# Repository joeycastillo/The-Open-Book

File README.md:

# The Open Book: Project Reboot

**A note from the project creator:** The Open Book was my first real electronics project; the earliest designs date to late 2019. I have learned a lot since those early days, and as such, here three years later, I am hitting reset. At this time the repository contains a version of the Open Book designed around the Raspberry Pi Pico. It's optimized for low part count and easy hand assembly, but it runs on AAA batteries and may not be as svelte as some folks might prefer. At a later date, I hope to design a followup with built-in LiPo charging and a slimmer profile, but at this time, this version of the book is the quickest path to getting hardware in people's hands so that we can start hacking on firmware together.

For details on how to build, test and use Open Book, I've [made documentation available here](https://www.oddlyspecificobjects.com/projects/openbook/).

The original Open Book repository has been archived in a branch called [original](https://github.com/joeycastillo/The-Open-Book/tree/original).

[The Open Book firmware, called libros, is under development here](https://github.com/joeycastillo/libros). It's a goddamn mess in some ways, and in dire need of some documentation, but for the moment it does do the job of presenting a list of books stored on an SD card, and letting you read them. The canonical format for books is plain text with the book title on the first line, OR plain text plus some front matter and some ASCII control codes for chapter breaks and formatting, [as documented here](https://www.oddlyspecificobjects.com/projects/openbook/#advanced-text-formatting).

## Original Introduction

As a society, we need an open source device for reading. Books are among the most important documents of our culture, yet the most popular and widespread devices we have for reading — the Kobo, the Nook, the Kindle and even the iPad — are closed devices, operating as small moving parts in a set of giant closed platforms whose owners' interests are not always aligned with readers'.

The Open Book aims to be a simple device that anyone with a soldering iron can build for themselves. The Open Book should be comprehensible: the reader should be able to look at it and understand, at least in broad strokes, how it works. It should be extensible, so that a reader with different needs can write code and add accessories that make the book work for them. It should be global, supporting readers of books in all the languages of the world. Most of all, it should be open, so that anyone can take this design as a starting point and use it to build a better book.

## State of the Book

At this time, the Pi Pico book is in decent shape if you want to try your hand at building it yourself. You will need to have two custom things fabricated: the **Open Book Main Board** (which you can get as a bare PCB) and the **Castellated E-Paper Driver** module (which you'll want to have done as a PCBA job). All the files you will need to send out for this can be found in the **Fabrication Files** folder in the project root:

* Upload `OSO-BOOK-C1-04-rounded.zip` to your PCB fabrication house of choice. It is designed to be a two-layer, 1 mm thick PCB, and you can use either an ENIG or lead-free HASL finish.
* If you plan to use JLCPCB's economic PCBA service, upload all three files in `OSO-BOOK-C2-01` to JLCPCB. Opt for a 1 mm thick lead-free HASL finish. Note that the board is slightly wider than it needs to be, just to meet the minimum size requirements for this service.
* If you plan to use PCBWay's PCBA service, upload all three files in `OSO-BOOK-C2-02` to PCBWay. Once again, opt for a 1 mm thick lead-free HASL finish. 

Other Parts: 

* Two of these [side mount buttons](https://www.digikey.com/en/products/detail/würth-elektronik/434351045816/5209090)
* One of these [side-mount switches](https://www.digikey.com/en/products/detail/c-k/JS102011SAQN/1640095)
* One [MEM2075 MicroSD card slot](https://www.digikey.com/en/products/detail/gct/MEM2075-00-140-01-A/9859614)
* One [GD25Q16C Flash chip](https://www.digikey.com/en/products/detail/gigadevice-semiconductor-hk-limited/GD25Q16CTIGR/9484675) with SOIC / SOP8 footprint.
* One [Keystone 1022 dual AAA battery holder](https://www.digikey.com/en/products/detail/keystone-electronics/1022/2137859) (you can get clones on Aliexpress for cheap)
* Two P-channel MOSFETS with SOT23 footprint (I use the DMG3415)
* Two 10kΩ resistors with 1206 footprint.
* Two 10µF capacitors with 1206 footprint (rated voltage >=6.3V).
* One 1µF capacitor with 0805 footprint (rated voltage >=6.3V).
* Seven through-hole slim tactile buttons (3mm by 6mm; [TL1107 type](https://www.digikey.com/en/products/detail/e-switch/TL1107AF130WQ/378976))
* One [GDEW042T2 grayscale e-paper display](https://buy-lcd.com/products/42inch-e-inkanel-spi-interface-buy-eaper-display). (Don't get the tri-color version; it'll end in heartbreak)
* And finally, one [Raspberry Pi Pico](https://www.digikey.com/en/products/detail/raspberry-pi/SC0915/13624793) board

The Open Book is open source hardware: you should feel free to build one yourself, order parts for ten and do a workshop at your local maker space, or even buy parts for fifty and sell them as kits. 

Please steal this book.

I plan to add more documentation in the new year, but until then, [this half-hour video walks through building one Open Book board in real-time](https://archive.org/details/live-from-the-oddly-specific-kitchen-table-assembling-the-pcbway-official-sponso).

### Forking and tweaking the boards

* Design files for the Open Book main board can be found in the `OSO-BOOK-C1` folder. It's a KiCad project.
* Design files for the castellated e-paper driver module can be found in the `OSO-BOOK-C2` folder. Alas, they are Eagle projects that predate my move to KiCad. There are two versions: an older version that was successfully fabricated with JLCPCB's economic PCBA service (`OSO-BOOK-C2-01`), and a newer version successfully fabricated using PCBWay's PCBA service (`OSO-BOOK-C2-02`). Both work great.

## License

 Different components of the project are licensed differently, see [LICENSE.md](https://github.com/joeycastillo/The-Open-Book/blob/main/LICENSE.md).

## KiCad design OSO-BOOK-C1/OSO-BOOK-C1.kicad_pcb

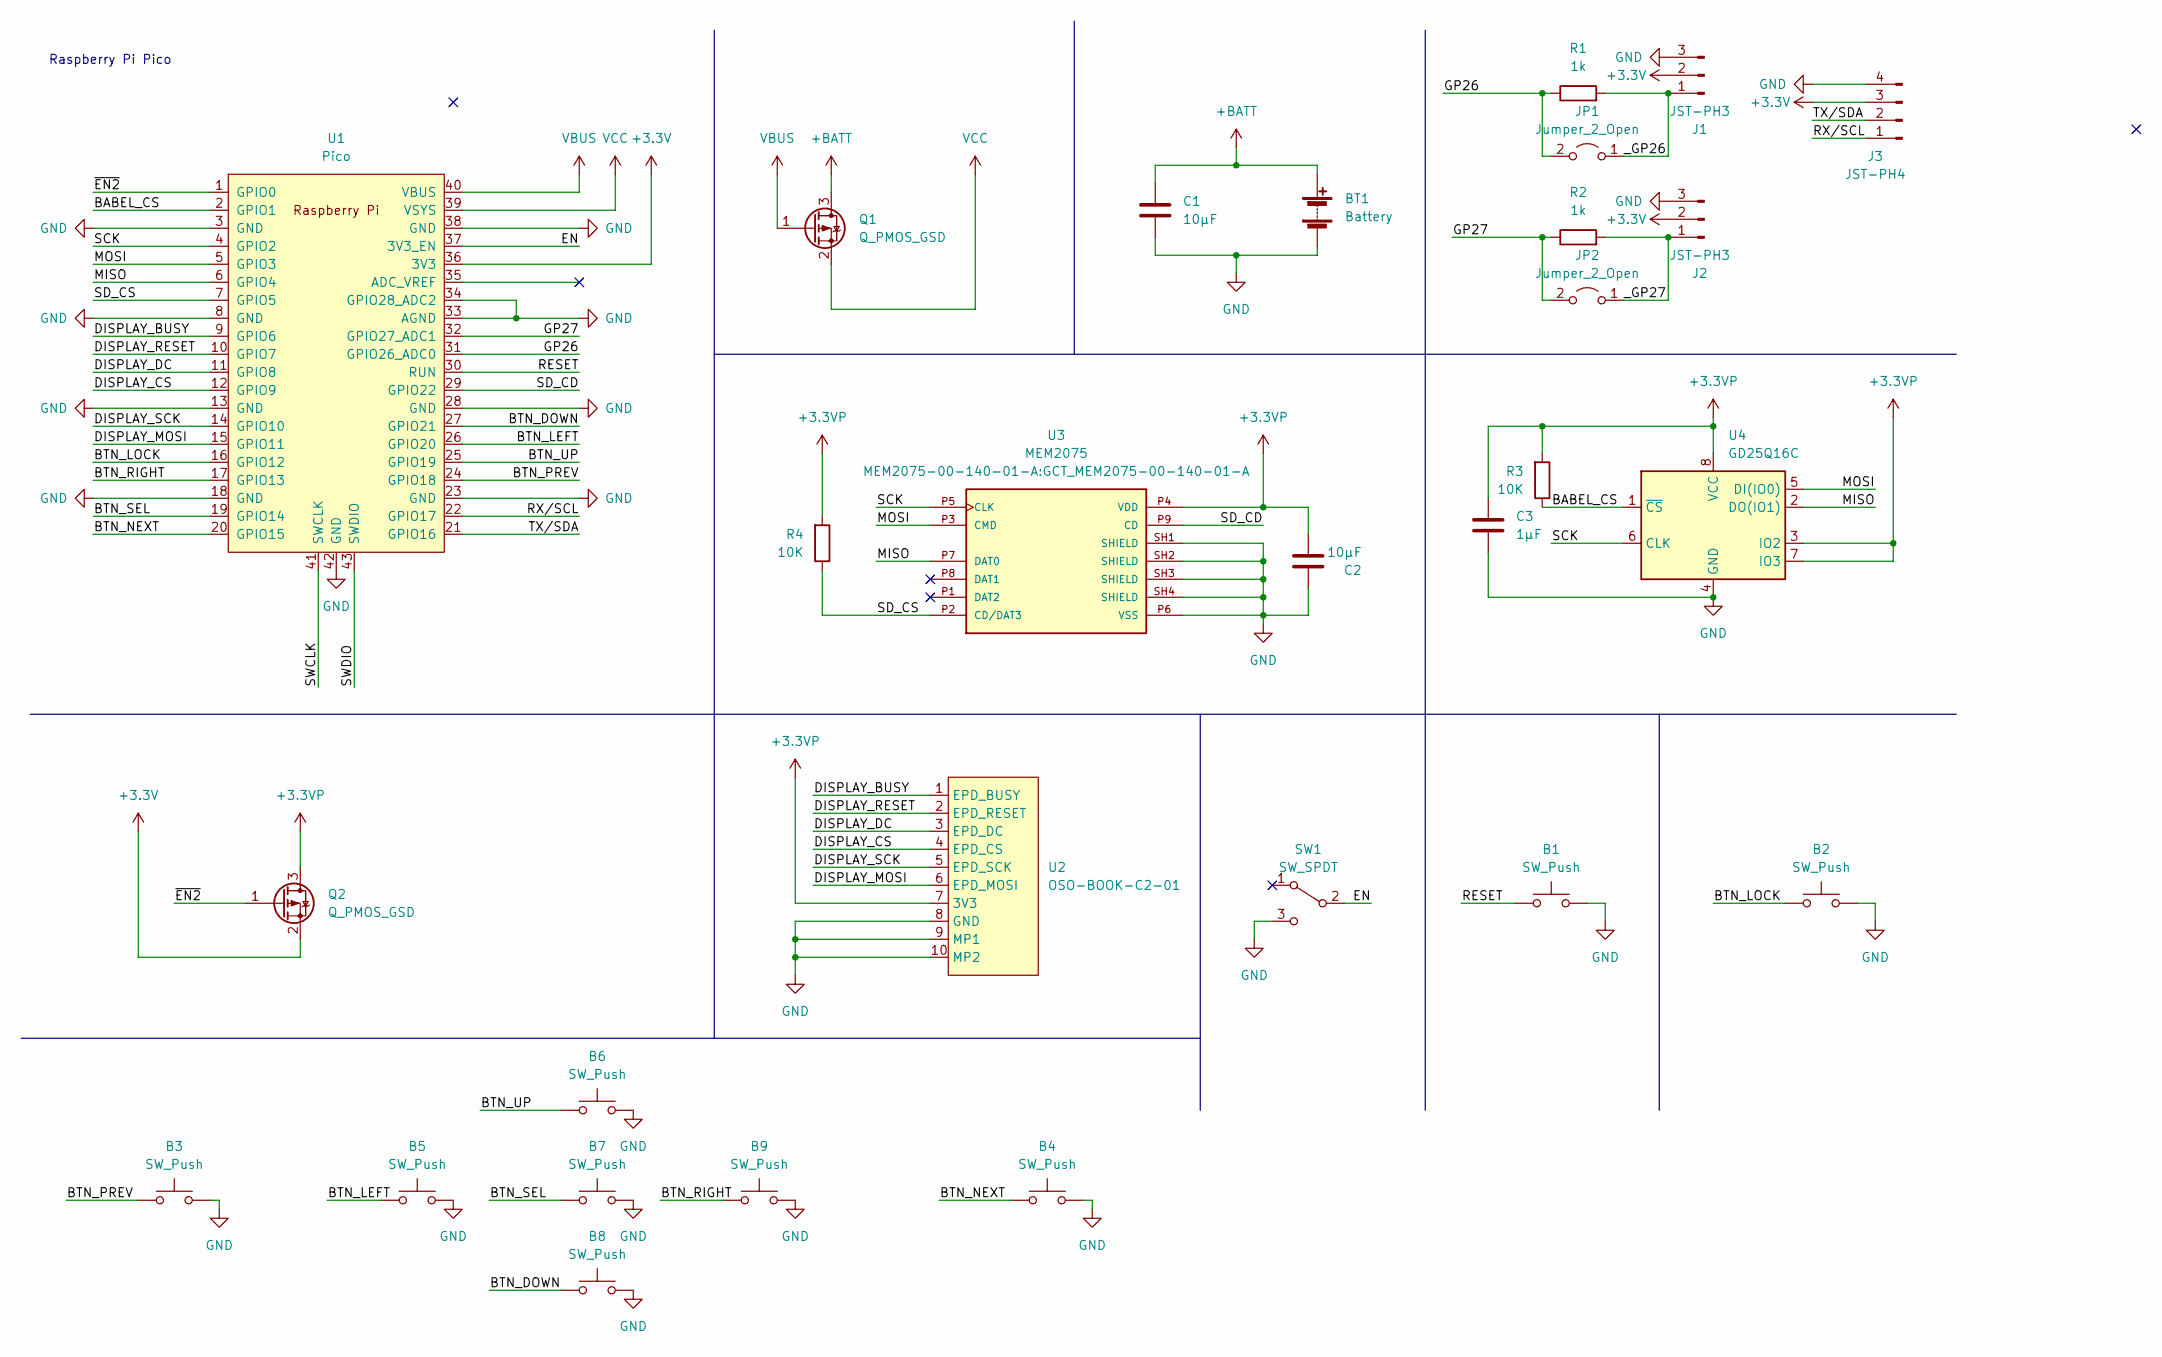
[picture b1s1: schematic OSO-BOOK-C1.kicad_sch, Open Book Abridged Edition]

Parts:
B1, B2: SW_Push; Panasonic_EVQPUJ_EVQPUA
B3, B4, B5, B6, B7, B8, B9: SW_Push; TACT_PANA-EVQ-BUTTONPAD
BT1: Battery; AAA_SMT
C1, C2: 10µF; C_1206_3216Metric_Pad1.33x1.80mm_HandSolder
C3: 1µF; C_0805_2012Metric_Pad1.18x1.45mm_HandSolder
J1, J2: JST-PH3; JST_PH_S3B-PH-SM4-TB_1x03-1MP_P2.00mm_Horizontal
J3: JST-PH4; JST_SH_SM04B-SRSS-TB_1x04-1MP_P1.00mm_Horizontal
JP1, JP2: Jumper_2_Open; SolderJumper-2_P1.3mm_Open_TrianglePad1.0x1.5mm
Q1, Q2: Q_PMOS_GSD; SOT-23_Handsoldering
R1, R2: 1k; R_0805_2012Metric_Pad1.20x1.40mm_HandSolder
R3, R4: 10K; R_1206_3216Metric_Pad1.30x1.75mm_HandSolder
SW1: SW_SPDT; SW_SPDT_CK-JS102011SAQN
U1: Pico; RPi_Pico_SMD
U2: OSO-BOOK-C2-01
U3: MEM2075; GCT_MEM2075-00-140-01-A; PARTREV A
U4: GD25Q16C; SOIC-8_3.9x4.9mm_P1.27mm

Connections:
+3.3VP: C2.2, C3.1, Q2.3 (D), R3.2, R4.2, U2.7 (3V3), U3.P4 (VDD), U4.3 (IO2), U4.7 (IO3), U4.8 (VCC)
+3V3: J1.2, J2.2, J3.3, Q2.2 (S), U1.36 (3V3)
+BATT: BT1.1 (+), C1.1, Q1.3 (D)
/BABEL_CS: R3.1, U1.2 (GPIO1), U4.1 (~CS)
/BTN_DOWN: B8.1, U1.27 (GPIO21)
/BTN_LEFT: B5.1, U1.26 (GPIO20)
/BTN_LOCK: B2.1, U1.16 (GPIO12)
/BTN_NEXT: B4.1, U1.20 (GPIO15)
/BTN_PREV: B3.1, U1.24 (GPIO18)
/BTN_RIGHT: B9.1, U1.17 (GPIO13)
/BTN_SEL: B7.1, U1.19 (GPIO14)
/BTN_UP: B6.1, U1.25 (GPIO19)
/DISPLAY_BUSY: U1.9 (GPIO6), U2.1 (EPD_BUSY)
/DISPLAY_CS: U1.12 (GPIO9), U2.4 (EPD_CS)
/DISPLAY_DC: U1.11 (GPIO8), U2.3 (EPD_DC)
/DISPLAY_MOSI: U1.15 (GPIO11), U2.6 (EPD_MOSI)
/DISPLAY_RESET: U1.10 (GPIO7), U2.2 (EPD_RESET)
/DISPLAY_SCK: U1.14 (GPIO10), U2.5 (EPD_SCK)
/EN: SW1.2 (B), U1.37 (3V3_EN)
/GP26: JP1.2 (B), R1.1, U1.31 (GPIO26_ADC0)
/GP27: JP2.2 (B), R2.1, U1.32 (GPIO27_ADC1)
/MISO: U1.6 (GPIO4), U3.P7 (DAT0), U4.2 (DO(IO1))
/MOSI: U1.5 (GPIO3), U3.P3 (CMD), U4.5 (DI(IO0))
/RESET: B1.1, U1.30 (RUN)
/RX/SCL: J3.1, U1.22 (GPIO17)
/SCK: U1.4 (GPIO2), U3.P5 (CLK), U4.6 (CLK)
/SD_CD: U1.29 (GPIO22), U3.P9 (CD)
/SD_CS: R4.1, U1.7 (GPIO5), U3.P2 (CD/DAT3)
/SWCLK: U1.41 (SWCLK)
/SWDIO: U1.43 (SWDIO)
/TX/SDA: J3.2, U1.21 (GPIO16)
/_GP26: J1.1, JP1.1 (A), R1.2
/_GP27: J2.1, JP2.1 (A), R2.2
/~EN2: Q2.1 (G), U1.1 (GPIO0)
GND: B1.2, B2.2, B3.2, B4.2, B5.2, B6.2, B7.2, B8.2, B9.2, BT1.2 (-), C1.2, C2.1, C3.2, J1.3, J2.3, J3.4, SW1.3 (C), U1.3 (GND), U1.8 (GND), U1.13 (GND), U1.18 (GND), U1.23 (GND), U1.28 (GND), U1.33 (AGND), U1.34 (GPIO28_ADC2), U1.38 (GND), U1.42 (GND), U2.8 (GND), U2.9 (MP1), U2.10 (MP2), U3.P6 (VSS), U3.SH1 (SHIELD), U3.SH2 (SHIELD), U3.SH3 (SHIELD), U3.SH4 (SHIELD), U4.4 (GND)
VBUS: Q1.1 (G), U1.40 (VBUS)
VCC: Q1.2 (S), U1.39 (VSYS)

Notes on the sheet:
Raspberry Pi Pico

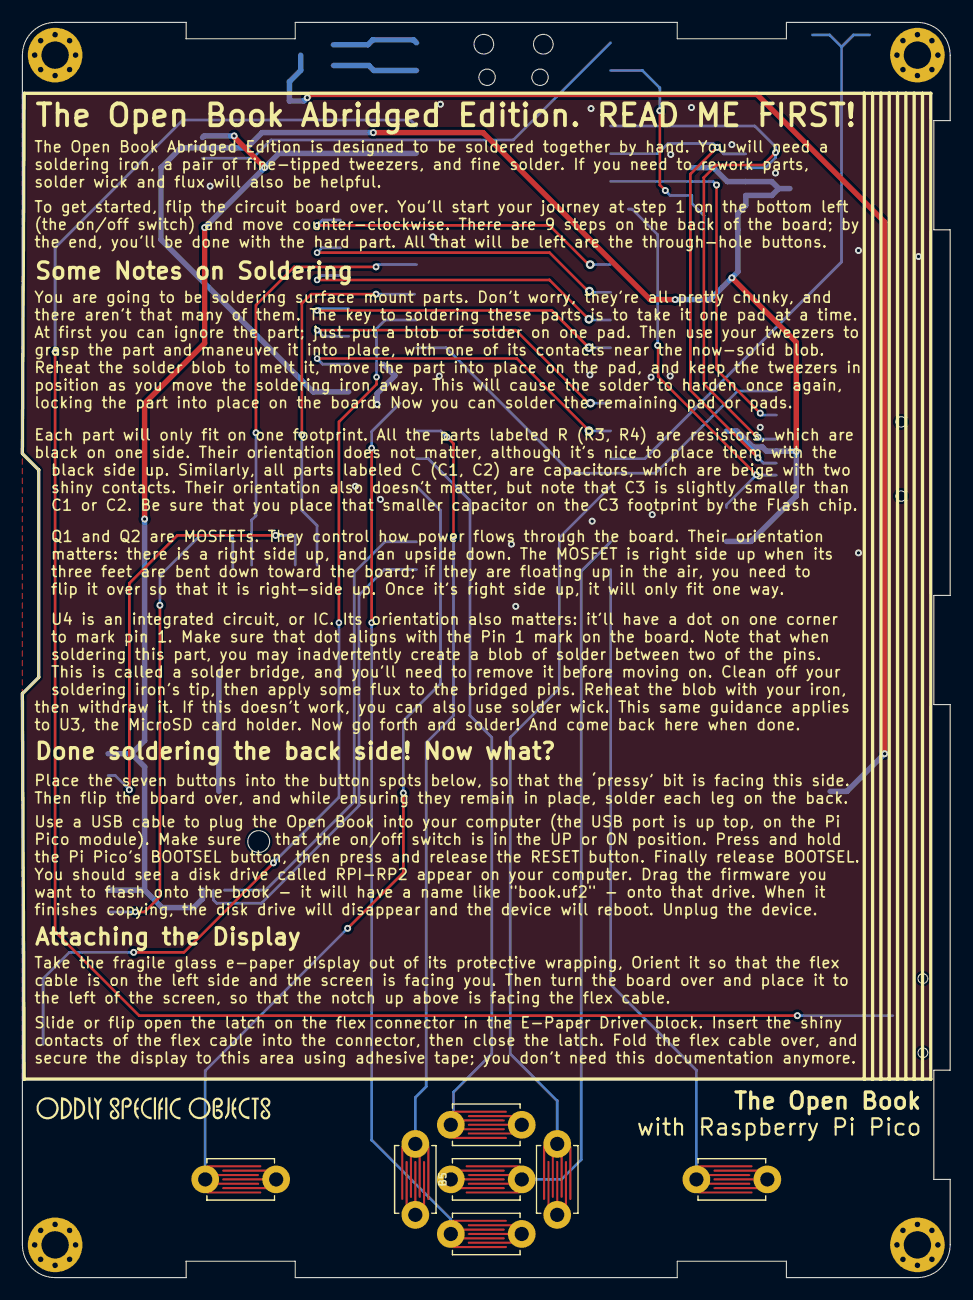
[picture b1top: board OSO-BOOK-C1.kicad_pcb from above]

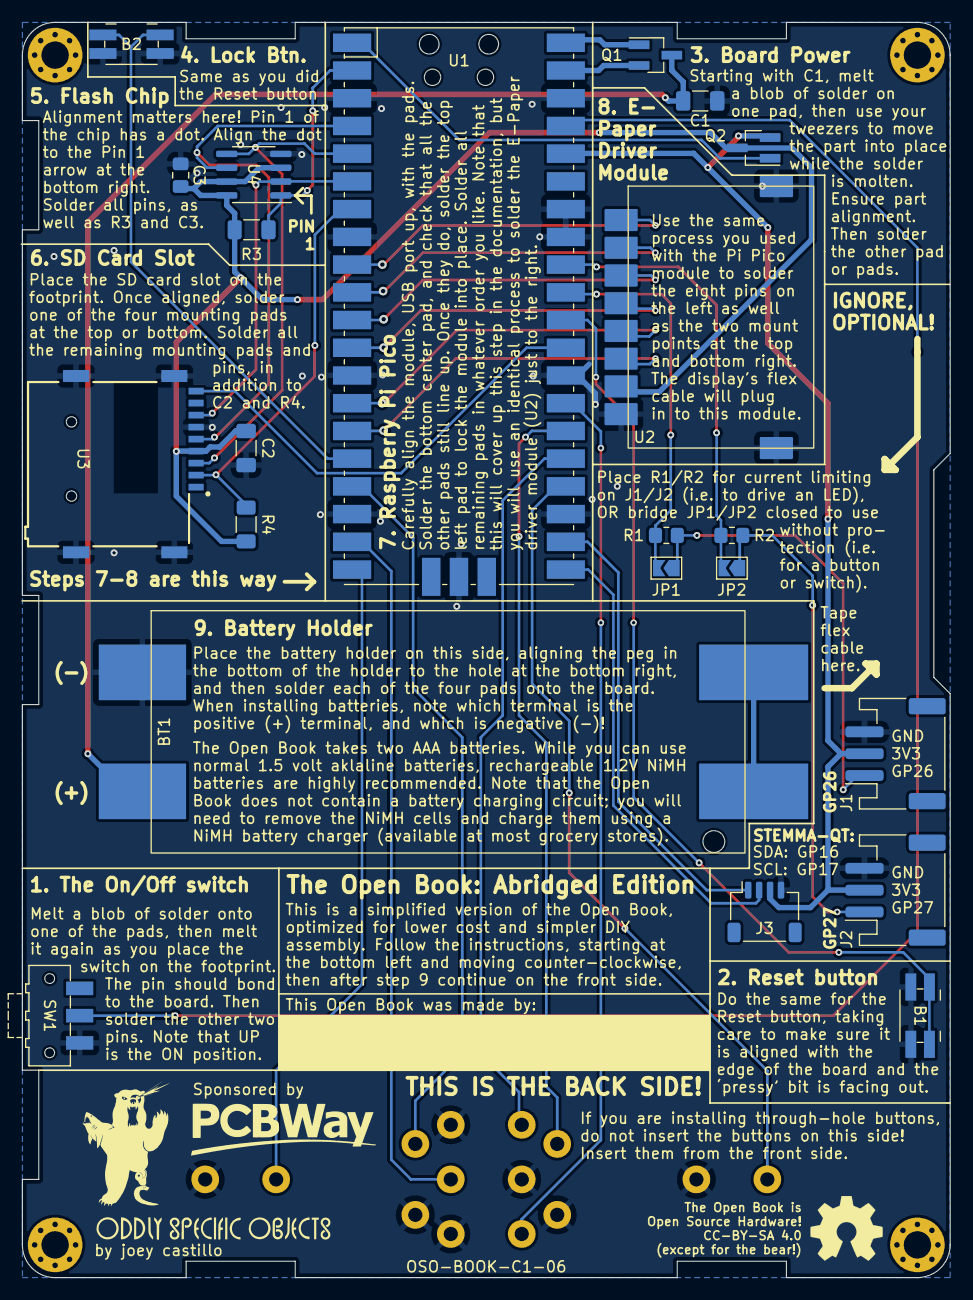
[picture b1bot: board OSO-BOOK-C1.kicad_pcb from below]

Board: 2 copper layers, 85.0 x 115.0 mm, 29 parts (22 on the bottom side), 35 nets.

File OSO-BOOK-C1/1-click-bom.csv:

References,Qty,Description,Manufacturer,MPN,Digikey,Mouser,RS,Newark,Farnell,LCSC,JLC Assembly
"B1, B2,",2,"Right-angle push button, SPST",,434351045816,732-7057-1-ND,710-434351045816,,,,,
"SW1,",1,"Right-angle slide switch, SPDT",,JS102011SAQN,401-1999-1-ND,611-JS102011SAQN,,,,,
"BT1,",1,Battery holder for 2x AAA cells,,1022,36-1022-ND,534-1022,,,,,
"Q1, Q2,",2,"P-MOSFET transistor, gate/source/drain",,DMG3415U-7,DMG3415UDIDKR-ND,621-DMG3415UQ-7,,,,,
"C1, C2,",2,"10µF capacitor, 1206",,CL31B106KQHNFNE,1276-3107-1-ND,187-CL31B106KQHNFNE,,,,,
"C3,",1,"1µF capacitor, 0805",,CL21B105KAFNNNE,1276-1066-1-ND,187-CL21B105KAFNNNF,,,,,
"R3, R4,",2,10KΩ resistor 1206,,RMCF1206JT10K0,RMCF1206JT10K0CT-ND,652-CR1206FX-1002ELF,,,,,
"U1,",1,Raspberry Pi Pico,,SC0918,2648-SC0918CT-ND,713-102110537,,,,,
"U3,",1,"MicroSD card slot, push/push",,MEM2075-00-140-01-A,2073-MEM2075-00-140-01-ACT-ND,640-MEM20750014001A,,,,,
"U4,",1,2 MB Flash memory chip,,GD25Q16CTIGR,1970-1010-1-ND,363-GD25Q16CTIGR,,,,,
"B3, B4, B5, B6, B7, B8, B9,",7,"Through-hole push button, SPST",,TL1107AF180WQ,EG2511-ND,612-TL1107,,,,,
"J1, J2,",2,STEMMA connector. OPTIONAL,,S3B-PH-SM4-TB(LF)(SN),455-1790-1-ND,,,,,,
"J3,",1,STEMMA QT connector. OPTIONAL,,BM04B-SRSS-TB(LF)(SN),455-1750-1-ND,,,,,,
"R1, R2,",2,"1k resistor, 0805. OPTIONAL",,RC0805JR-071KL,311-1.0KARCT-ND,603-RC0805JR-071KL,,,,,
"U2,",1,Oddly Specific castellated E-paper driver module,,OSO-BOOK-C2-01,,,,,,,
Display,1,4.2 Inch B&W E-paper Panel,,GDEW042T2,,,,,,,

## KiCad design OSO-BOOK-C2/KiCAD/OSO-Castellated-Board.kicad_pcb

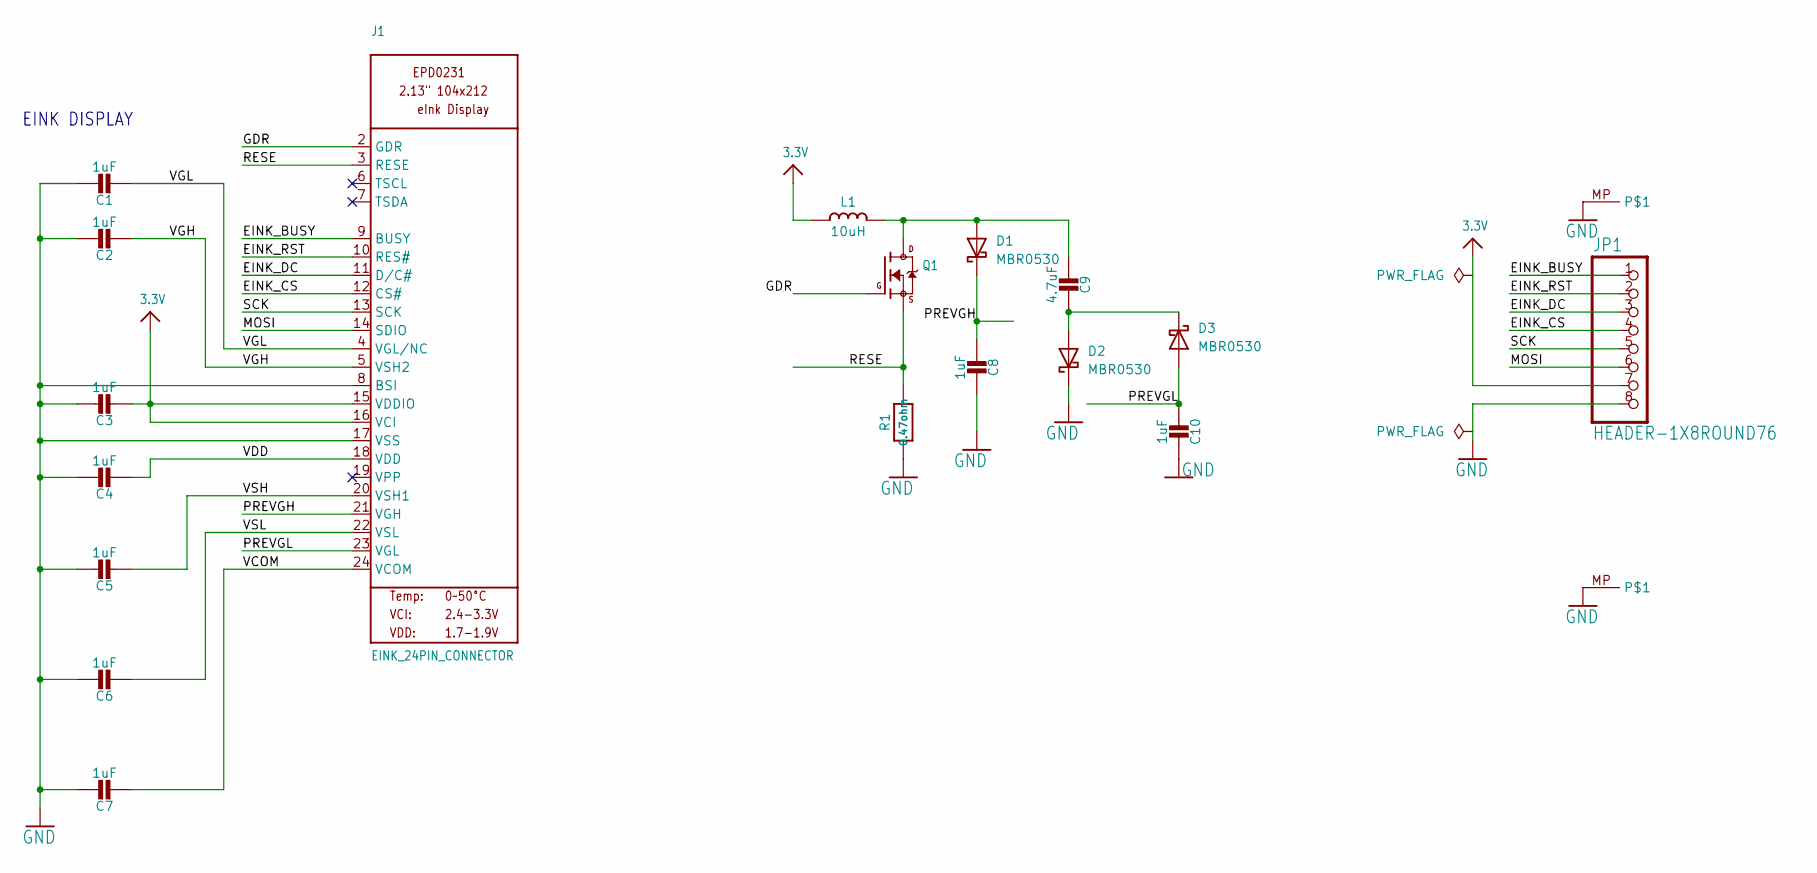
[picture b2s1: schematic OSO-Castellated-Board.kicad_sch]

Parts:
C1, C2, C3, C4, C5, C6, C7, C8, C10: 1uF; C_0805_2012Metric
C9: 4.7uF; C_0805_2012Metric
D1, D2, D3: MBR0530; D_SOD-123
J1: EINK_24PIN_CONNECTOR; AFC07-S24ECC-00
JP1: HEADER-1X8ROUND76; Castellated-Connnector-1x8
L1: 10uH; L_0805_2012Metric
Q1: IRLML0100; SOT-23
R1: 0.47ohm; R_0402_1005Metric
U$1, U$2: BIGOVAL; Oval-Mounting-Point

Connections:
3.3V: C3.2, J1.15 (VDDIO), J1.16 (VCI), JP1.7, L1.1
/EINK_BUSY: J1.9 (BUSY), JP1.1
/EINK_CS: J1.12 (CS#), JP1.4
/EINK_DC: J1.11 (D/C#), JP1.3
/EINK_RST: J1.10 (RES#), JP1.2
/GDR: J1.2 (GDR), Q1.1 (G)
/MOSI: J1.14 (SDIO), JP1.6
/PREVGH: C8.1, D1.1 (K), J1.21 (VGH)
/PREVGL: C10.1, D3.2 (A), J1.23 (VGL)
/RESE: J1.3 (RESE), Q1.2 (S), R1.1
/SCK: J1.13 (SCK), JP1.5
/VCOM: C7.2, J1.24 (VCOM)
/VDD: C4.2, J1.18 (VDD)
/VGH: C2.2, J1.5 (VSH2)
/VGL: C1.2, J1.4 (VGL/NC)
/VSH: C5.2, J1.20 (VSH1)
/VSL: C6.2, J1.22 (VSL)
GND: C1.1, C2.1, C3.1, C4.1, C5.1, C6.1, C7.1, C8.2, C10.2, D2.1 (K), J1.8 (BSI), J1.17 (VSS), JP1.8, R1.2, U$1.MP, U$2.MP
unnamed: C9.1, D1.2 (A), L1.2, Q1.3 (D)
unnamed: C9.2, D2.2 (A), D3.1 (K)

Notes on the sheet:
EINK DISPLAY

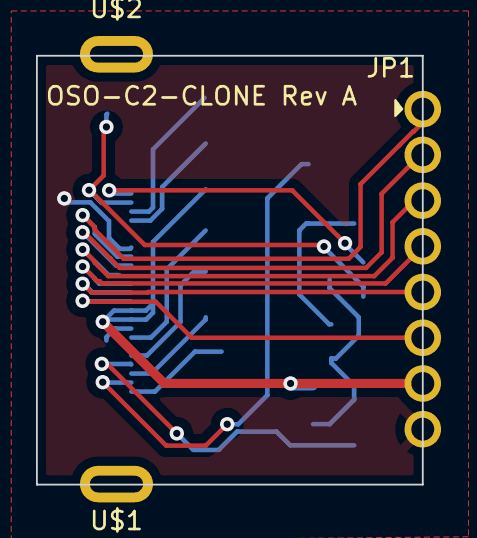
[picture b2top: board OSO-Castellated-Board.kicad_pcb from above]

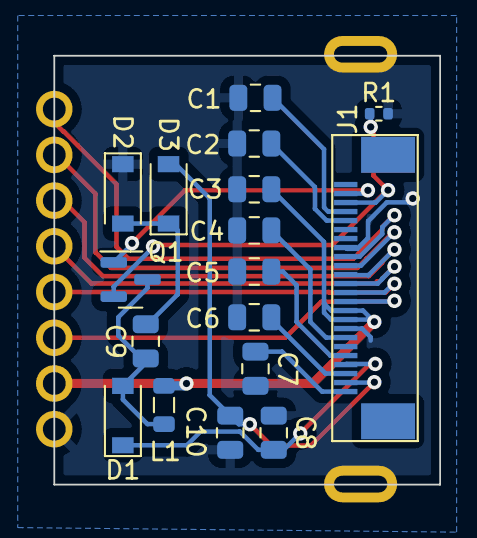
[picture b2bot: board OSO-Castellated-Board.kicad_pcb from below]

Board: 2 copper layers, 21.4 x 23.8 mm, 20 parts (17 on the bottom side), 20 nets.

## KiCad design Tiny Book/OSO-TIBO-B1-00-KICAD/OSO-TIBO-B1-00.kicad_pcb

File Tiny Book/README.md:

# The Tiny Book

Okay I'm going to be completely honest: I have wandered pretty far from the original prompt with this one. The theory was let's make a less expensive, smaller version of the Open Book with as much of its functionality as possible. With variant B, tiny book has instead become a this very quixotic experiment in form and intent, as well as a playground for new tech like [Good Display's touch screen 2.7" EPD](https://zh-tw.buyepaper.com/products/e-ink-touchscreen-27inch-spi-interface-china-e-ink-manufacturer). 

Variant A (with the cap touch slider) is still here but the touch screen kind of renders it moot. Variant B might be a dead end too, but I think it'll have been worth building for the lessons learned along the way. You could also probably redesign it around an ESP32 or NRF52840 and wind up with something more useful, but there are enough new things in this that I figured I'd stick with the SAMD51 for now since I know the chip so well.

- Features that are basically the same as the Open Book:
    - Battery charging
    - Indicator LEDs
    - 4MB QSPI Flash (up from 2MB)
    - MicroSD slot
    - Enable switch
    - Lock button
    - Reset button
    - Serial port
    - VBAT and VBUS monitors
    - Neopixel

- Features that are similar, and the differences:
    - E-Paper screen. Still has partial refresh, but it's smaller (2.7" instead of 4.2").
    - Instead of seven buttons on the front, the E-Paper display has a capacitive touch matrix that detects touches and gestures (and has an interrupt pin).
    - Microcontroller: it's still a SAMD51 with native USB and the same amount of Flash and RAM, but in a QFN48 package, so fewer pins (and sadly less hand-solderability).
    - The I2C port is now JST-SH (STEMMA-QT) due to size constraints.

- Things that are gone, and strategies for doing without:
    - One STEMMA port instead of two, but it's a really versatile pin. It's a DAC pin so you can speaker with it, or configure it as analog input for a mic or potentiometer, PWM it for an LED, run a Neopixel strip or use it as GPIO for a button.
    - Babel chip. The CircuitPython Babel library supports just putting babel.bin on the QSPI flash chip (and since it's twice the size, you'll still have the same amount of space left over for code).
    - Feather compatibility. Sorry. It would be rad to be able to support FeatherWings but there's just not enough room (or pins).

In the course of this experiment, I ran across a very old design concept that imagined a hinged device with a second e-paper screen on a separate board. So I threw one together, using a [9-pin connector](https://www.adafruit.com/product/4350) (like Adafruit uses on the [MONSTER M4SK](https://www.adafruit.com/product/4343)) to bring over SPI, I2C and one extra signal. A SAMD09 on the secondary board (running Adafruit's Seesaw firmware) gives us more pins for more toys.

- Features that got moved to the secondary board or nerfed.
    - Headphone jack (mono instead of stereo) now lives on the secondary board. I sense that the audio quality may not be as good, since the signal has to travel over a 9-pin connector right next to the I2C signals, but we'll find out.
    - Inline mic input moves over with the headphone jack, but alas there is no longer any provision for recording sound (I removed the mic preamp since there's no spare wire to send a mic signal back to the main board). You can still bias the mic input pin and detect up to three types of button presses from the inline button.

- New features on the secondary board
    - A second 2.7" e-paper display. Pads are there for a touch screen and it's in theory connected to pins on the SAMD09 that *could* support I2C. But this would require some kind of passthrough of I2C messages that I'd have to implement in the SAMD09 firmware. My plan is to use a cheaper non-touchscreen display and only have the main screen be a touch screen.
    - An extra status LED. I'm thinking blue?
    - Speaking of LED's: a PWM-enabled bank of five white LED's along the right (left?) side of the board. I call it a reading light, but they'll shine right at your face if you turn them on. There might be some way to fold the device that coaxes them into illuminating the main screen.
    - Speaking of folding the device: a voltage divider labeled "Hinge?" that I might be able to turn into some kind of hinge position detector using a flex PCB. I honestly have no idea.
    - A real-time clock, because I had room (and because I think this could actually make for a sweet clock).
    - A buzzer for making noises (because it might as well be a sweet alarm clock).
    - A light sensor (because I had a pin leftover).

oh also because i haven't written down the board nomenclature anywhere, this is what i mean by OSO-TIBO-B1-00:

- OSO = Oddly Specific Objects
- TIBO = TIny BOok, the project name
- B = Variant, A-Z, some major version of the board with a specific piece of tech or form factor that makes it unique.
- 1 = Subassembly, 1-9. I doubt I'll ever come up with a project that involves more than 9 PCBs.
- 00 = revision, 00-99. Usually starts at 01, but if I'm really unsure of something I'll start at 00.

I'll update this once the boards come in and I actually assemble one of these.

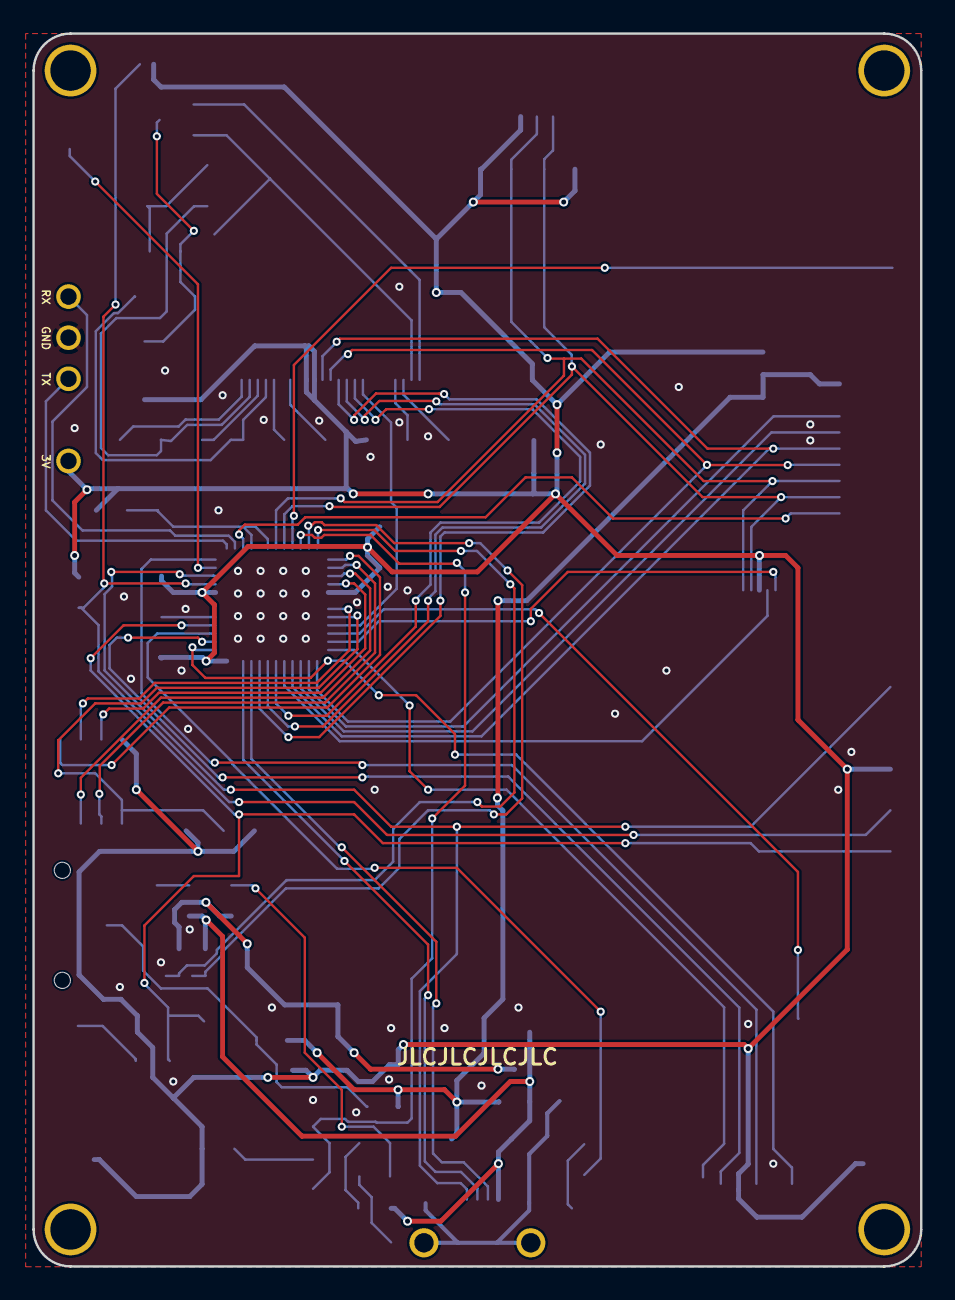
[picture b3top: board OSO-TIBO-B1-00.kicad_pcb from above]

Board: 2 copper layers, 54.9 x 76.2 mm, 90 parts (0 on the bottom side), 66 nets.

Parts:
ACCESSORY_PORT1: JST PH 3; JSTPH3
BTN_LOCK1: SWITCH_PUSHBUTTONC&K_KSS; BTN_CK_KSS
BTN_RESET1: SWITCH_PUSHBUTTONC&K_KSS; BTN_CK_KSS
C1, C2, C6: 10µF; 0805-NO
C3, C8, C9: 1uF; 0805-NO
C4, C7, C26: 10uF; 0805-NO
C5: 1µF; 0805-NO
C10, C11, C12, C14, C15, C16, C17: 1uF; 0805_10MGAP
C13: 0.1uF; 0805_10MGAP
C18, C19, C20, C21, C22, C23: 1uF/25V; 0805_10MGAP
C24: 4.7uF/25V; 0805-NO
C25: 10uF; 0805_10MGAP
C27: 4.5nF; 0805-NO
CHG1: AMBER; CHIPLED_0805
D1: MBR120; SOD-123
D2, D3, D4: MBR0530; SOD-123
D5: 3.6V; SOD-123
ENABLE_SWITCH1: JS102011SAQN; SW_JS102011SAQN
FB1: Ferrite; 0805
FID1, FID2, FID3, FID4: FIDUCIAL_1MM
FUL1: GREEN; CHIPLED_0805
GOLD_ORB_SM1: OSHWLOGOLOGO5MM; OSHW_5MM
I2C_PORT1: SM04B-SRSS-TB(LF)(SN); JST_SM04B-SRSS-TB(LF)(SN)
J2: 10118193-0001LF; FCI_10118193-0001LF
JP1: PINHD-1X3; 1X03
JP2: PINHD-1X1; 1X01
JP3: HEADER-1X9_JSTSH; JST_SH9
L2: 10uH; MICROBUILDER_INDUCTOR_4X4MM_NR401_BIGPADS
LED1: RED; CHIPLED_0805
MICROSD1: MICROSD
NEOPIXEL1: WS2812B_4020
Q1: DMG341; SOT23-R
Q2: IRLML0100; SOT23-3
R1, R3, R7, R8, R10, R13, R14: 10K; 0805-NO
R2: 100K; 0805-NO
R4: 100K; EXBV8V
R5, R6, R11: 1K; 0805-NO
R9: 100; 0805_10MGAP
R12: 0.47ohm; 0805_10MGAP
R15: 1K; _0805MP
R16: 1M; 0805-NO
SENSE1: SMD5; SMD2,54-5,08
SJ1: SOLDERJUMPER_2WAY; SOLDERJUMPER_2WAY_OPEN_NOPASTE
TP1, TP2, TP3, TP4, TP5: TESTPOINTROUND2MMNO; TESTPOINT_ROUND_2MM_NO
U1: AP2112-3.3; SOT23-5
U2: MCP73831T-2ACI/OT; SOT23-5
U3: ATSAMD51G18A-MUT; QFN48_7X7MC
U4: GD25Q32C; MICROBUILDER_SOIC8_150MIL
U$1, U$4, U$5, U$7: MOUNTINGHOLE2.5; MOUNTINGHOLE_2.5_PLATED
U$31: EINK_DISPLAY_TOUCH; EINK_DISPLAY_2_7_IN_TOUCH
U$37: OSO_WORDMARK_THREELINE_450MIL_1000DPI
U$44: OSO_BEAR_250X360MIL_1000DPI
X1: JSTPH; JSTPH2

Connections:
+3V3: ACCESSORY_PORT1.2, C2.1, C3.1, C4.1, C5.1, C7.2, C8.2, C10.2, C12.2, C14.1, C17.2, C25.1, C26.1, FB1.1, I2C_PORT1.2, JP2.1, L2.P$1, MICROSD1.4, NEOPIXEL1.2, R7.2, R8.2, R10.2, R13.1, R14.1, SJ1.1, TP3.P$1, U1.5, U3.17, U3.36, U3.44, U4.8, U$31.15, U$31.16, U$31.28
/OSO-TIBO-B1-00_1/A0_AUDIO: JP3.9, U3.3
/OSO-TIBO-B1-00_1/A2_HINGE_SENSOR: SENSE1.1, U3.9
/OSO-TIBO-B1-00_1/A4_VBATMON: R4.1, R4.2, U3.11
/OSO-TIBO-B1-00_1/A5_VBUSMON: R4.3, R4.4, U3.12
/OSO-TIBO-B1-00_1/D2_A3_ACCESSORY: D5.C, R15.2, U3.10
/OSO-TIBO-B1-00_1/D3_LOCK_BUTTON: BTN_LOCK1.P$2, U3.47
/OSO-TIBO-B1-00_1/D5_SWDIO_USBID: J2.4, TP1.P$1, U3.46
/OSO-TIBO-B1-00_1/D13_LED: R11.1, U3.39
/OSO-TIBO-B1-00_1/D16_9PIN_CS: JP3.4, U3.27
/OSO-TIBO-B1-00_1/D17_9PIN_DC_SERCOM3_MISO: JP3.3, U3.26
/OSO-TIBO-B1-00_1/D30_QSPI_SCK: U3.19, U4.6
/OSO-TIBO-B1-00_1/D31_QSPI_CS: R10.1, U3.20, U4.1
/OSO-TIBO-B1-00_1/D32_QSPI_DATA[0]: U3.13, U4.5
/OSO-TIBO-B1-00_1/D33_QSPI_DATA[1]: U3.14, U4.2
/OSO-TIBO-B1-00_1/D34_QSPI_DATA[2]: U3.15, U4.3
/OSO-TIBO-B1-00_1/D35_QSPI_DATA[3]: U3.16, U4.7
/OSO-TIBO-B1-00_1/USB_N: J2.2, U3.33
/OSO-TIBO-B1-00_1/USB_P: J2.3, U3.34
/OSO-TIBO-B1-00_1/~RESET: C13.2, R8.1, R9.2, TP5.P$1, U3.40
/OSO-TIBO-B1-00_2/GDR: Q2.1, U$31.2
/OSO-TIBO-B1-00_2/PREVGH: C20.1, D4.C, U$31.21
/OSO-TIBO-B1-00_2/PREVGL: C22.1, D3.A, U$31.23
/OSO-TIBO-B1-00_2/RESE: Q2.2, R12.1, U$31.3
/OSO-TIBO-B1-00_2/VCOM: C23.2, U$31.24
/OSO-TIBO-B1-00_2/VDD: C18.2, U$31.18
/OSO-TIBO-B1-00_2/VGH: C16.2, U$31.5
/OSO-TIBO-B1-00_2/VGL: C15.2, U$31.4
/OSO-TIBO-B1-00_2/VSH: C19.2, U$31.20
/OSO-TIBO-B1-00_2/VSL: C21.2, U$31.22
AVCC: C9.2, FB1.2, U3.4, U3.6
D0_SERCOM1_RX: JP1.3, U3.2
D1_SERCOM1_TX: JP1.1, U3.1
D4_TOUCHINT: U3.23, U$31.26
D6_SDCS: MICROSD1.2, U3.24
D7_SDCD: MICROSD1.CD1, U3.22
D8_SWCLK_NEOPIX: NEOPIXEL1.1, R7.1, TP4.P$1, U3.45
D9_EINK_CS: U3.32, U$31.12
D10_EINK_DC: U3.31, U$31.11
D11_EINK_RST: U3.30, U$31.10
D12_EINK_BUSY: U3.21, U$31.9
D14_TOUCH_RST: U3.29, U$31.27
D15_SERCOM3_MOSI: JP3.5, U3.28, U$31.14
D18_SERCOM3_SCK: JP3.6, U3.25, U$31.13
D25_SERCOM4_SDA: I2C_PORT1.3, JP3.7, R14.2, U3.7, U$31.30
D26_SERCOM4_SCL: I2C_PORT1.4, JP3.8, R13.2, U3.8, U$31.29
D27_SERCOM5_MISO: MICROSD1.7, U3.37
D28_SERCOM5_MOSI: MICROSD1.3, U3.38
D29_SERCOM5_SCK: MICROSD1.5, U3.48
EN: ENABLE_SWITCH1.2, R1.1, U1.3
GND: ACCESSORY_PORT1.1, BTN_LOCK1.P$1, BTN_RESET1.P$1, C1.2, C2.2, C3.2, C4.2, C5.2, C6.2, C7.1, C8.1, C9.1, C10.1, C11.1, C12.1, C13.1, C14.2, C15.1, C16.1, C17.1, C18.1, C19.1, C20.2, C21.1, C22.2, C23.1, C25.2, C26.2, C27.2, D2.C, D5.A, ENABLE_SWITCH1.1, FUL1.C, I2C_PORT1.1, J2.5, JP1.2, JP3.2, LED1.C, MICROSD1.6, MICROSD1.MT1, MICROSD1.MT2, NEOPIXEL1.4, R2.2, R3.2, R4.5, R4.7, R12.2, R16.2, TP2.P$1, U1.2, U2.2, U3.5, U3.18, U3.35, U3.42, U3.49, U4.4, U$31.8, U$31.17, U$31.25, X1.1
unnamed: ACCESSORY_PORT1.3, R15.1
unnamed: BTN_RESET1.P$2, R9.1
unnamed: C11.2, U3.41
unnamed: C24.1, D4.A, L2.P$2, Q2.3
unnamed: C24.2, D2.A, D3.C
unnamed: C27.1, J2.S1, J2.S2, J2.S3, J2.S4, J2.S5, J2.S6, R16.1
unnamed: CHG1.C, R6.1
unnamed: FUL1.A, R5.1
unnamed: JP3.1, SJ1.2
unnamed: LED1.A, R11.2
unnamed: R3.1, U2.5
unnamed: R5.2, R6.2, U2.1
V+: C1.1, D1.C, Q1.2, R1.2, SJ1.3, U1.1
VBAT: C6.1, Q1.3, R4.6, U2.3, X1.2
VBUS: CHG1.A, D1.A, J2.1, Q1.1, R2.1, R4.8, U2.4

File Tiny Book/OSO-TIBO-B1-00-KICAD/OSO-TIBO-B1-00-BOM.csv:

Reference, Quantity, Value, Footprint, Datasheet
ACCESSORY_PORT1 ,1,"JST PH 3","OSO-TIBO-B1-00:JSTPH3",""
BTN_LOCK1 BTN_RESET1 ,2,"SWITCH_PUSHBUTTONC&K_KSS","OSO-TIBO-B1-00:BTN_CK_KSS",""
C1 C2 C6 ,3,"10µF","OSO-TIBO-B1-00:0805-NO",""
C10 C11 C12 C14 C15 C16 C17 ,7,"1uF","OSO-TIBO-B1-00:0805_10MGAP",""
C13 ,1,"0.1uF","OSO-TIBO-B1-00:0805_10MGAP",""
C18 C19 C20 C21 C22 C23 ,6,"1uF/25V","OSO-TIBO-B1-00:0805_10MGAP",""
C24 ,1,"4.7uF/25V","OSO-TIBO-B1-00:0805-NO",""
C25 ,1,"10uF","OSO-TIBO-B1-00:0805_10MGAP",""
C27 ,1,"4.5nF","OSO-TIBO-B1-00:0805-NO",""
C3 C8 C9 ,3,"1uF","OSO-TIBO-B1-00:0805-NO",""
C5 ,1,"1µF","OSO-TIBO-B1-00:0805-NO",""
C26 C4 C7 ,3,"10uF","OSO-TIBO-B1-00:0805-NO",""
CHG1 ,1,"AMBER","OSO-TIBO-B1-00:CHIPLED_0805",""
D1 ,1,"MBR120","OSO-TIBO-B1-00:SOD-123",""
D2 D3 D4 ,3,"MBR0530","OSO-TIBO-B1-00:SOD-123",""
D5 ,1,"3.6V","OSO-TIBO-B1-00:SOD-123",""
ENABLE_SWITCH1 ,1,"JS102011SAQN","OSO-TIBO-B1-00:SW_JS102011SAQN",""
FB1 ,1,"Ferrite","OSO-TIBO-B1-00:0805",""
FID1 FID2 FID3 FID4 ,4,"FIDUCIAL_1MM","OSO-TIBO-B1-00:FIDUCIAL_1MM",""
FUL1 ,1,"GREEN","OSO-TIBO-B1-00:CHIPLED_0805",""
GOLD_ORB_SM1 ,1,"OSHWLOGOLOGO5MM","OSO-TIBO-B1-00:OSHW_5MM",""
I2C_PORT1 ,1,"SM04B-SRSS-TB(LF)(SN)","OSO-TIBO-B1-00:JST_SM04B-SRSS-TB(LF)(SN)",""
J2 ,1,"10118193-0001LF","OSO-TIBO-B1-00:FCI_10118193-0001LF",""
JP1 ,1,"PINHD-1X3","OSO-TIBO-B1-00:1X03",""
JP2 ,1,"PINHD-1X1","OSO-TIBO-B1-00:1X01",""
JP3 ,1,"HEADER-1X9_JSTSH","OSO-TIBO-B1-00:JST_SH9",""
L2 ,1,"10uH","OSO-TIBO-B1-00:MICROBUILDER_INDUCTOR_4X4MM_NR401_BIGPADS",""
LED1 ,1,"RED","OSO-TIBO-B1-00:CHIPLED_0805",""
MICROSD1 ,1,"MICROSD","OSO-TIBO-B1-00:MICROSD",""
NEOPIXEL1 ,1,"WS2812B_4020","OSO-TIBO-B1-00:WS2812B_4020",""
Q1 ,1,"DMG341","OSO-TIBO-B1-00:SOT23-R",""
Q2 ,1,"IRLML0100","OSO-TIBO-B1-00:SOT23-3",""
R1 R10 R13 R14 R3 R7 R8 ,7,"10K","OSO-TIBO-B1-00:0805-NO",""
R12 ,1,"0.47ohm","OSO-TIBO-B1-00:0805_10MGAP",""
R15 ,1,"1K","OSO-TIBO-B1-00:_0805MP",""
R16 ,1,"1M","OSO-TIBO-B1-00:0805-NO",""
R2 ,1,"100K","OSO-TIBO-B1-00:0805-NO",""
R4 ,1,"100K","OSO-TIBO-B1-00:EXBV8V",""
R11 R5 R6 ,3,"1K","OSO-TIBO-B1-00:0805-NO",""
R9 ,1,"100","OSO-TIBO-B1-00:0805_10MGAP",""
SENSE1 ,1,"SMD5","OSO-TIBO-B1-00:SMD2,54-5,08",""
SJ1 ,1,"SOLDERJUMPER_2WAY","OSO-TIBO-B1-00:SOLDERJUMPER_2WAY_OPEN_NOPASTE",""
TP1 TP2 TP3 TP4 TP5 ,5,"TESTPOINTROUND2MMNO","OSO-TIBO-B1-00:TESTPOINT_ROUND_2MM_NO",""
U$1 U$4 U$5 U$7 ,4,"MOUNTINGHOLE2.5","OSO-TIBO-B1-00:MOUNTINGHOLE_2.5_PLATED",""
U$31 ,1,"EINK_DISPLAY_TOUCH","OSO-TIBO-B1-00:EINK_DISPLAY_2_7_IN_TOUCH",""
U1 ,1,"AP2112-3.3","OSO-TIBO-B1-00:SOT23-5",""
U2 ,1,"MCP73831T-2ACI/OT","OSO-TIBO-B1-00:SOT23-5",""
U3 ,1,"ATSAMD51G18A-MUT","OSO-TIBO-B1-00:QFN48_7X7MC",""
U4 ,1,"GD25Q32C","OSO-TIBO-B1-00:MICROBUILDER_SOIC8_150MIL",""
X1 ,1,"JSTPH","OSO-TIBO-B1-00:JSTPH2",""

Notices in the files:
OSO-BOOK-C1/OSO-BOOK-C1.kicad_pcb:
CC-BY-SA 4.0
Tiny Book/OSO-TIBO-B2-00-KICAD/OSO-TIBO-B2-00.kicad_pcb:
CC-BY Bon-
